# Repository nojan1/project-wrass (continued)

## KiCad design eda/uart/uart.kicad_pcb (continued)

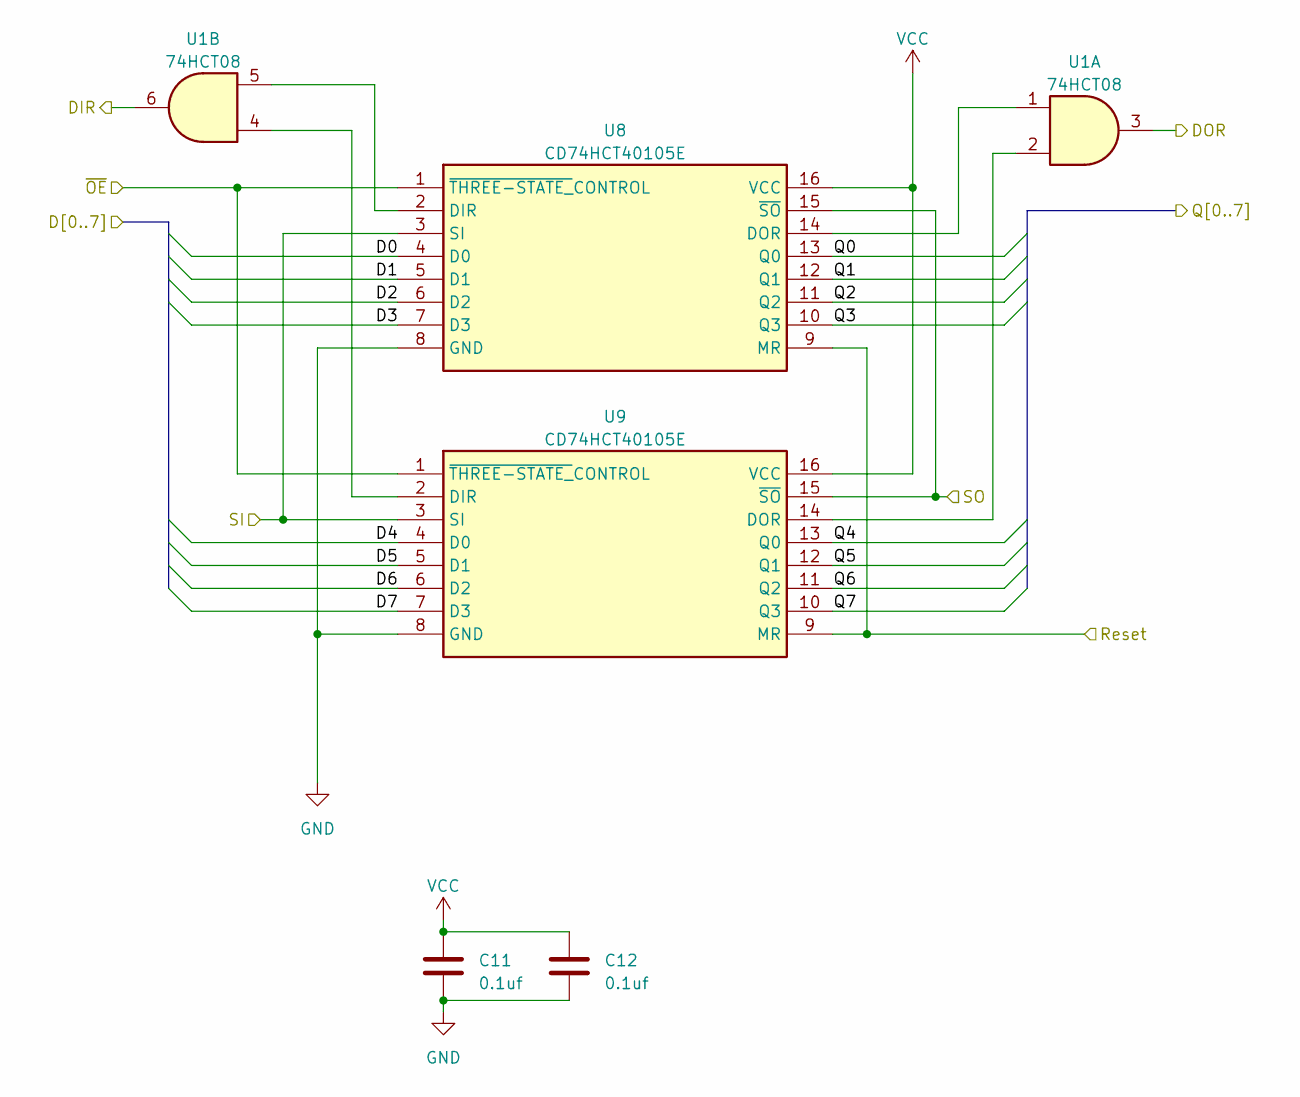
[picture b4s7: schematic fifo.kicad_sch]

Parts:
C11, C12: 0.1uf; C_Disc_D3.8mm_W2.6mm_P2.50mm
U1: 74HCT08; DIP-14_W7.62mm
U8, U9: CD74HCT40105E; DIP-16_W7.62mm; Manufacturer_Part_Number CD74HCT40105E; Mouser Part Number 595-CD74HCT40105E

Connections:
/Expansion header/D0: U8.4 (D0); also elsewhere on the board
/Expansion header/D1: U8.5 (D1); also elsewhere on the board
/Expansion header/D2: U8.6 (D2); also elsewhere on the board
/Expansion header/D3: U8.7 (D3); also elsewhere on the board
/Expansion header/D4: U9.4 (D0); also elsewhere on the board
/Expansion header/D5: U9.5 (D1); also elsewhere on the board
/Expansion header/D6: U9.6 (D2); also elsewhere on the board
/Expansion header/D7: U9.7 (D3); also elsewhere on the board
/address_decode/TransmitEnable: U8.3 (SI), U9.3 (SI); also elsewhere on the board
/recieve/DataAvailable: U1.11; also elsewhere on the board
/recieve/RecieveBufferFull: U1.8; also elsewhere on the board
/recieve/Reset: U8.9 (MR), U9.9 (MR); also elsewhere on the board
/transmit/FIFO Transmit/DOR: U1.3; also elsewhere on the board
/transmit/FIFO Transmit/Q0: U8.13 (Q0); also elsewhere on the board
/transmit/FIFO Transmit/Q1: U8.12 (Q1); also elsewhere on the board
/transmit/FIFO Transmit/Q2: U8.11 (Q2); also elsewhere on the board
/transmit/FIFO Transmit/Q3: U8.10 (Q3); also elsewhere on the board
/transmit/FIFO Transmit/Q4: U9.13 (Q0); also elsewhere on the board
/transmit/FIFO Transmit/Q5: U9.12 (Q1); also elsewhere on the board
/transmit/FIFO Transmit/Q6: U9.11 (Q2); also elsewhere on the board
/transmit/FIFO Transmit/Q7: U9.10 (Q3); also elsewhere on the board
/transmit/InputBufferFull: U1.6; also elsewhere on the board
/transmit/~LatchShiftRegisters: U8.15 (~SO), U9.15 (~SO); also elsewhere on the board
GND: C11.2, C12.2, U8.1 (~THREE-STATE_CONTROL), U8.8 (GND), U9.1 (~THREE-STATE_CONTROL), U9.8 (GND); also elsewhere on the board
unnamed: U1.5, U8.2 (DIR)
unnamed: U1.1, U8.14 (DOR)
unnamed: U1.4, U9.2 (DIR)
unnamed: U1.2, U9.14 (DOR)
unnamed 91: U1.10; also elsewhere on the board
unnamed 92: U1.12; also elsewhere on the board
unnamed 93: U1.9; also elsewhere on the board
unnamed 94: U1.13; also elsewhere on the board
VCC: C11.1, C12.1, U8.16 (VCC), U9.16 (VCC); also elsewhere on the board

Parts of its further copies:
C13, C14: 0.1uf; C_Disc_D3.8mm_W2.6mm_P2.50mm
U13, U14: CD74HCT40105E; DIP-16_W7.62mm; Manufacturer_Part_Number CD74HCT40105E; Mouser Part Number 595-CD74HCT40105E

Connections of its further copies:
/Expansion header/D0: U13.13 (Q0); also elsewhere on the board
/Expansion header/D1: U13.12 (Q1); also elsewhere on the board
/Expansion header/D2: U13.11 (Q2); also elsewhere on the board
/Expansion header/D3: U13.10 (Q3); also elsewhere on the board
/Expansion header/D4: U14.13 (Q0); also elsewhere on the board
/Expansion header/D5: U14.12 (Q1); also elsewhere on the board
/Expansion header/D6: U14.11 (Q2); also elsewhere on the board
/Expansion header/D7: U14.10 (Q3); also elsewhere on the board
/address_decode/~RecieveEnable: U13.1 (~THREE-STATE_CONTROL), U14.1 (~THREE-STATE_CONTROL); also elsewhere on the board
/recieve/FIFO Recieve/SI: U13.3 (SI), U14.3 (SI); also elsewhere on the board
/recieve/FIFO Recieve/SO: U13.15 (~SO), U14.15 (~SO); also elsewhere on the board
/recieve/ID0: U13.4 (D0); also elsewhere on the board
/recieve/ID1: U13.5 (D1); also elsewhere on the board
/recieve/ID2: U13.6 (D2); also elsewhere on the board
/recieve/ID3: U13.7 (D3); also elsewhere on the board
/recieve/ID4: U14.4 (D0); also elsewhere on the board
/recieve/ID5: U14.5 (D1); also elsewhere on the board
/recieve/ID6: U14.6 (D2); also elsewhere on the board
/recieve/ID7: U14.7 (D3); also elsewhere on the board
/recieve/Reset: U13.9 (MR), U14.9 (MR); also elsewhere on the board
GND: C13.2, C14.2, U13.8 (GND), U14.8 (GND); also elsewhere on the board
unnamed 91: U13.2 (DIR); also elsewhere on the board
unnamed 92: U13.14 (DOR); also elsewhere on the board
unnamed 93: U14.2 (DIR); also elsewhere on the board
unnamed 94: U14.14 (DOR); also elsewhere on the board
VCC: C13.1, C14.1, U13.16 (VCC), U14.16 (VCC); also elsewhere on the board

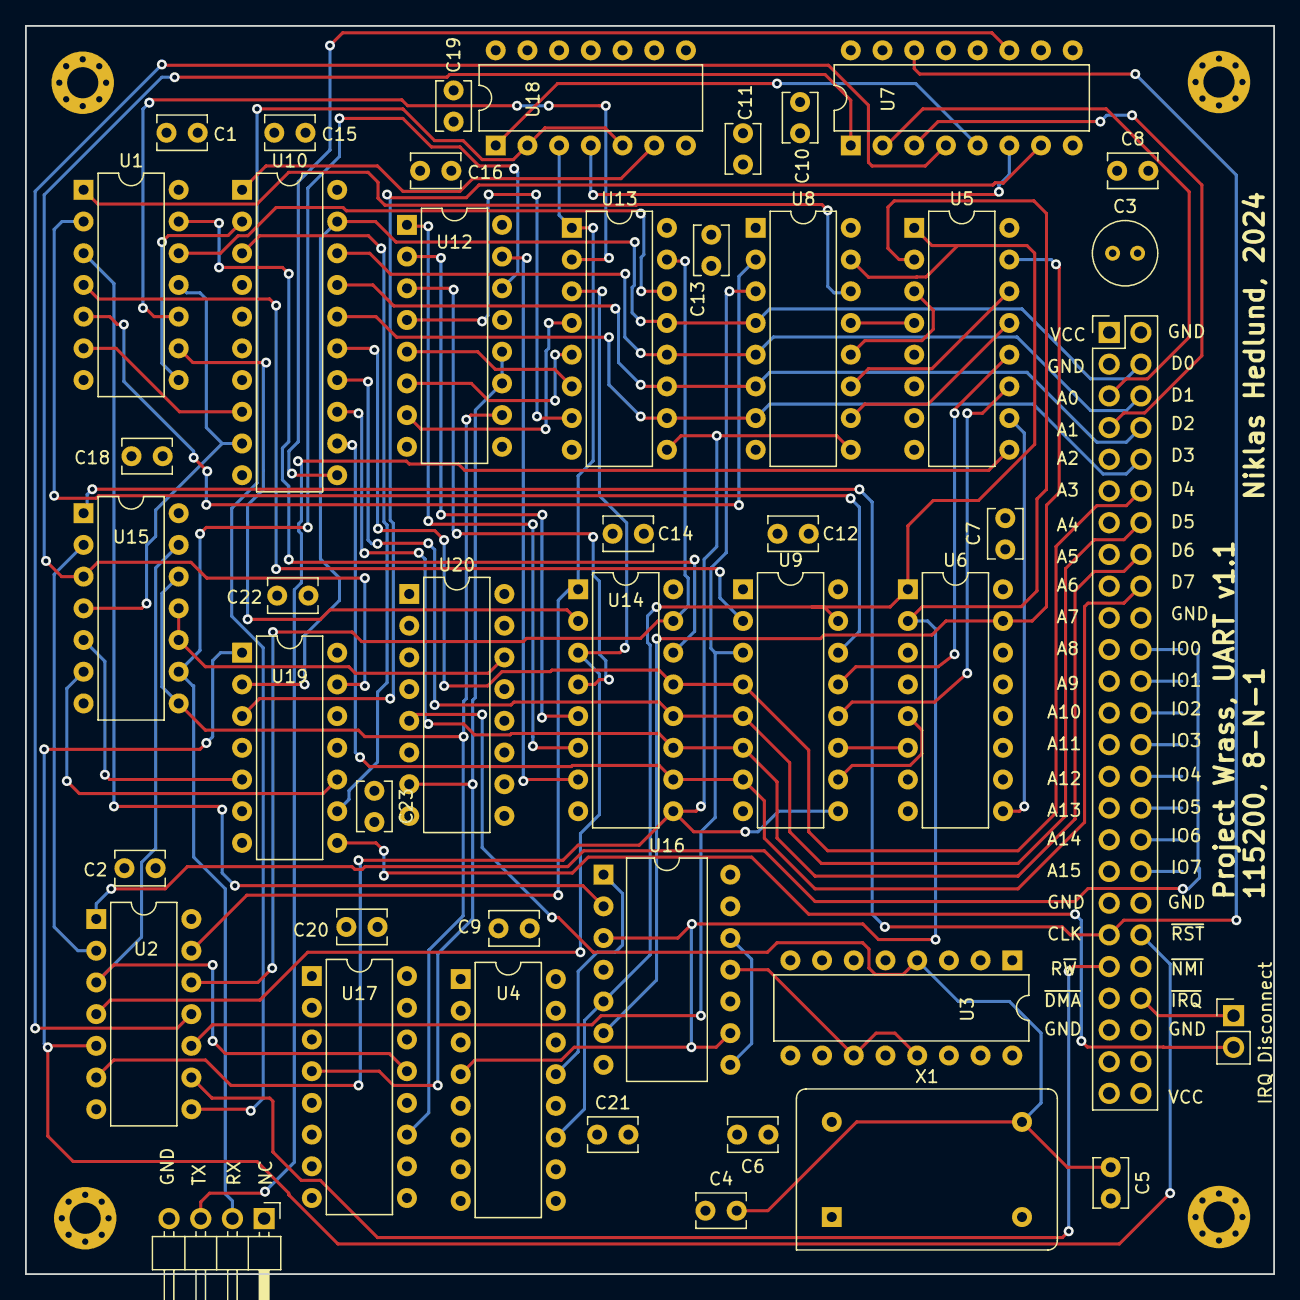
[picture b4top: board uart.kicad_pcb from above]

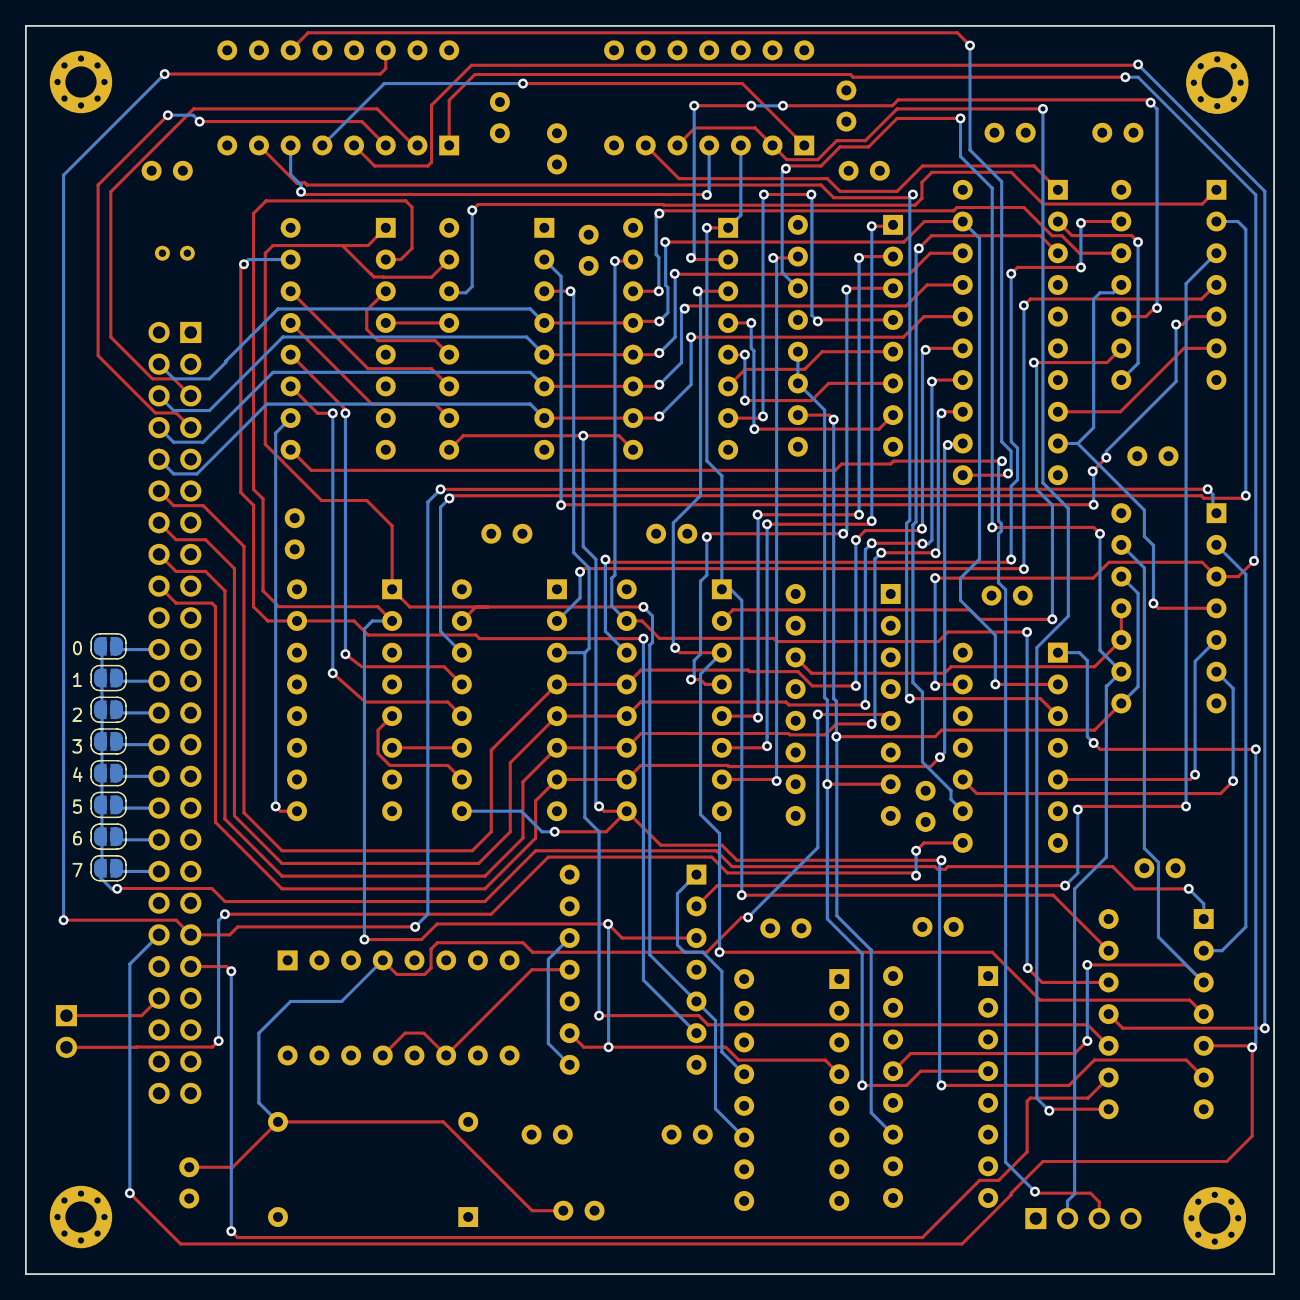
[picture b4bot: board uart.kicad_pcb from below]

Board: 4 copper layers, 100.0 x 100.0 mm, 57 parts (8 on the bottom side), 85 nets.

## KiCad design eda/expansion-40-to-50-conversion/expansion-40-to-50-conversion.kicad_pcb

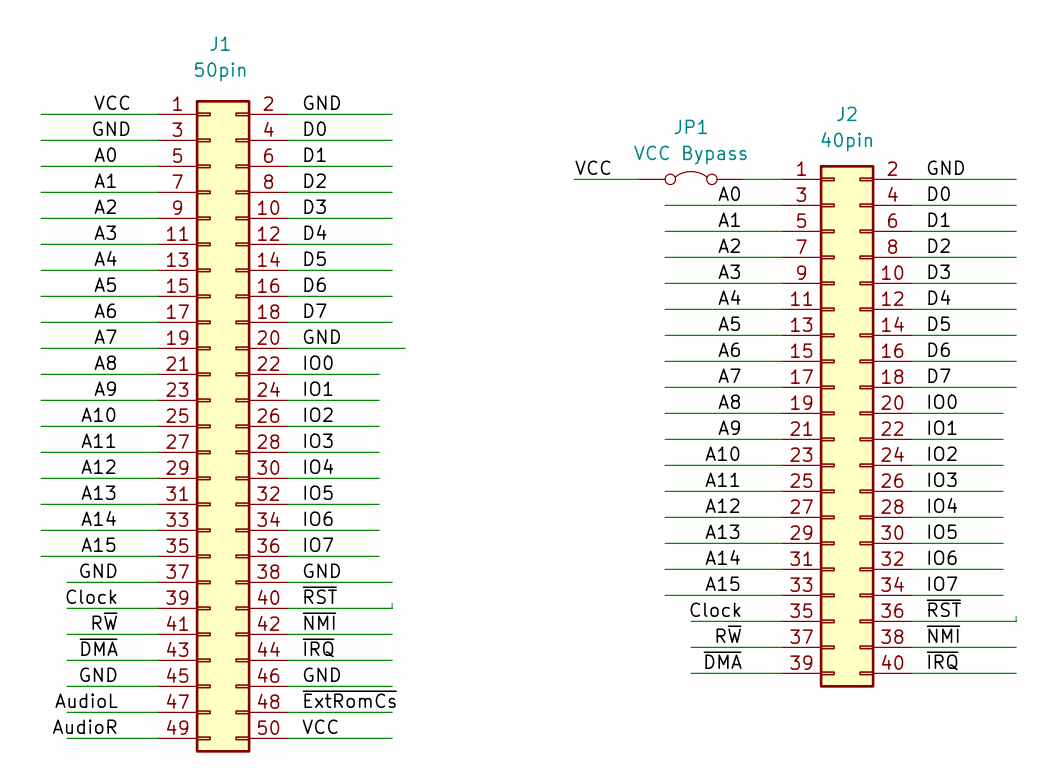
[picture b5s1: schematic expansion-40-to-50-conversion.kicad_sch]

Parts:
J1: 50pin; PinHeader_2x25_P2.54mm_Vertical
J2: 40pin; PinHeader_2x20_P2.54mm_Vertical
JP1: VCC Bypass; PinHeader_1x02_P2.54mm_Horizontal

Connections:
/A0: J1.5, J2.3
/A1: J1.7, J2.5
/A2: J1.9, J2.7
/A3: J1.11, J2.9
/A4: J1.13, J2.11
/A5: J1.15, J2.13
/A6: J1.17, J2.15
/A7: J1.19, J2.17
/A8: J1.21, J2.19
/A9: J1.23, J2.21
/A10: J1.25, J2.23
/A11: J1.27, J2.25
/A12: J1.29, J2.27
/A13: J1.31, J2.29
/A14: J1.33, J2.31
/A15: J1.35, J2.33
/AudioL: J1.47
/AudioR: J1.49
/Clock: J1.39, J2.35
/D0: J1.4, J2.4
/D1: J1.6, J2.6
/D2: J1.8, J2.8
/D3: J1.10, J2.10
/D4: J1.12, J2.12
/D5: J1.14, J2.14
/D6: J1.16, J2.16
/D7: J1.18, J2.18
/GND: J1.2, J1.3, J1.20, J1.37, J1.38, J1.45, J1.46, J2.2
/IO0: J1.22, J2.20
/IO1: J1.24, J2.22
/IO2: J1.26, J2.24
/IO3: J1.28, J2.26
/IO4: J1.30, J2.28
/IO5: J1.32, J2.30
/IO6: J1.34, J2.32
/IO7: J1.36, J2.34
/R~W: J1.41, J2.37
/VCC: J1.1, J1.50, JP1.1 (A)
/~DMA: J1.43, J2.39
/~ExtRomCs: J1.48
/~IRQ: J1.44, J2.40
/~NMI: J1.42, J2.38
/~RST: J1.40, J2.36
unnamed: J2.1, JP1.2 (B)

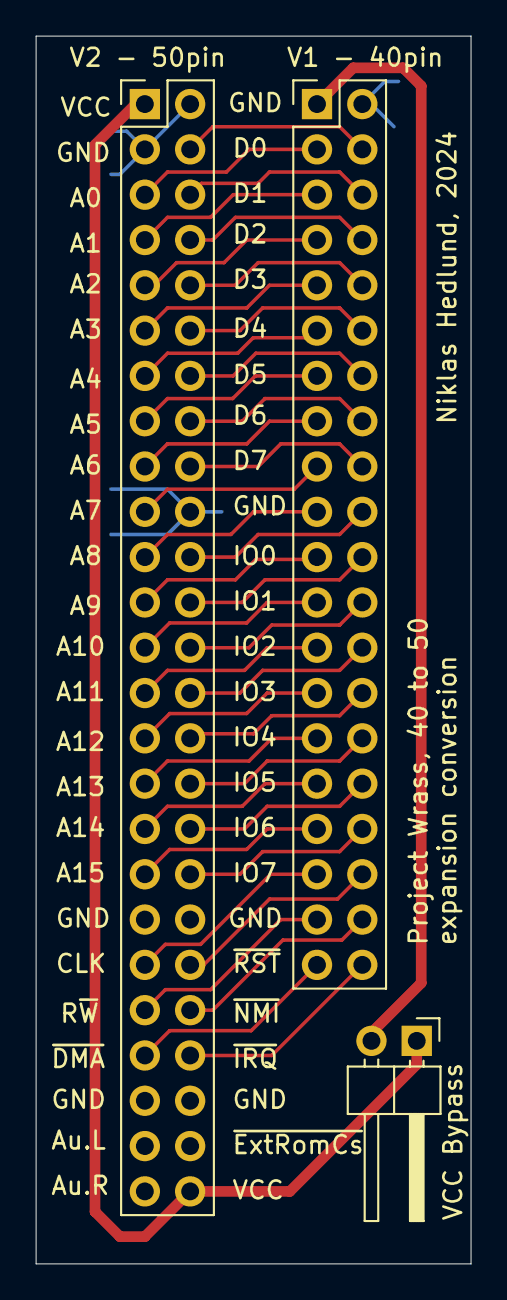
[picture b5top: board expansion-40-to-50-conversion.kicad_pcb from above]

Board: 2 copper layers, 24.4 x 68.8 mm, 3 parts (0 on the bottom side), 41 nets.

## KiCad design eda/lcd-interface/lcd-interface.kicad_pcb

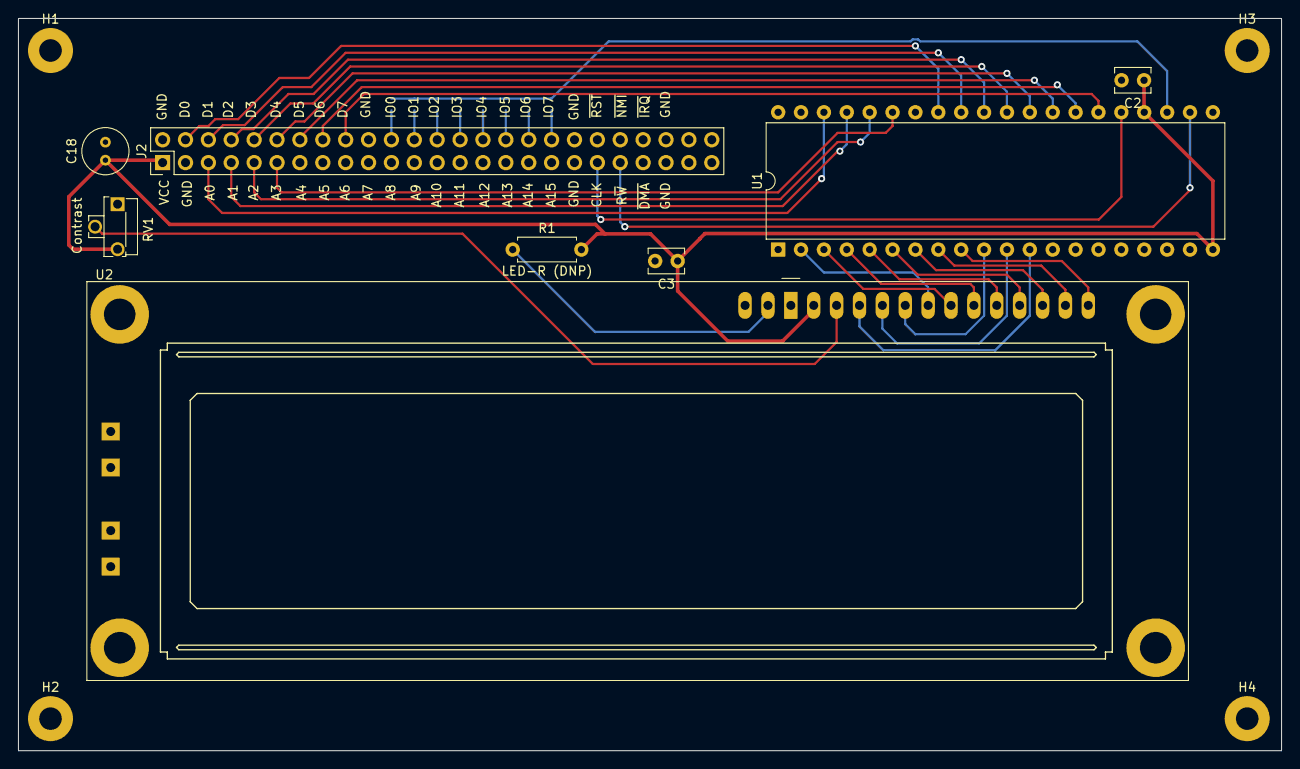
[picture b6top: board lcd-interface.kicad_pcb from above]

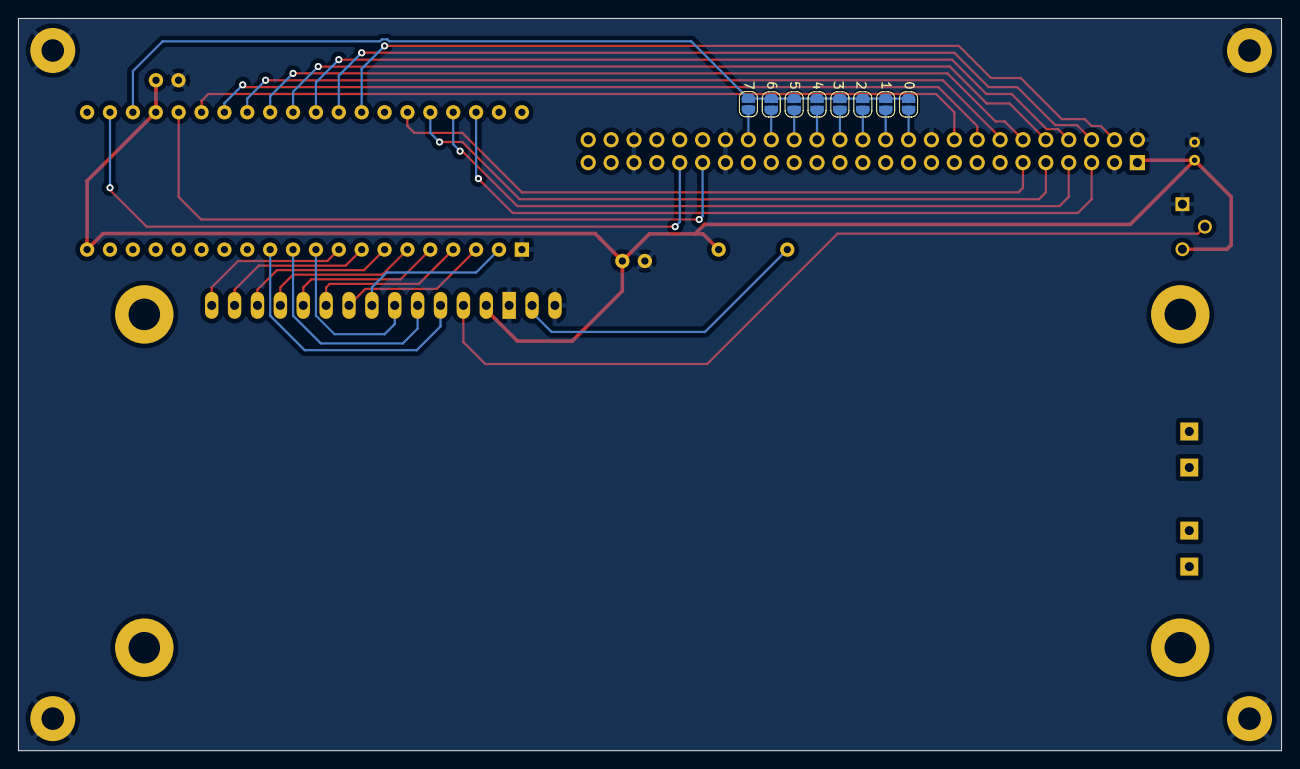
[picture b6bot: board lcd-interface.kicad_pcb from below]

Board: 2 copper layers, 140.2 x 81.3 mm, 20 parts (8 on the bottom side), 39 nets.

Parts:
C2, C3: 100nf; C_Disc_D3.8mm_W2.6mm_P2.50mm
C18: 100nf; C_Radial_D5.0mm_H7.0mm_P2.00mm
H1, H2, H3, H4: MountingHole_Pad; MountingHole_2.5mm_Pad
J2: Conn_02x25_Odd_Even; PinHeader_2x25_P2.54mm_Vertical
JP1, JP2, JP3, JP4, JP5, JP6, JP7, JP8: SolderJumper_2_Open; SolderJumper-2_P1.3mm_Open_RoundedPad1.0x1.5mm
R1: LED-R (DNP); R_Axial_DIN0207_L6.3mm_D2.5mm_P7.62mm_Horizontal
RV1: Contrast; Potentiometer_Runtron_RM-063_Horizontal
U1: W65C22SxP; DIP-40_W15.24mm
U2: LCD-016N002L

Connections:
/Clock: J2.39, U1.25 (ϕ2)
/Expansion header/A0: J2.5, U1.38 (RS0)
/Expansion header/A1: J2.7, U1.37 (RS1)
/Expansion header/A2: J2.9, U1.36 (RS2)
/Expansion header/A3: J2.11, U1.35 (RS3)
/Expansion header/D0: J2.4, U1.33 (D0)
/Expansion header/D1: J2.6, U1.32 (D1)
/Expansion header/D2: J2.8, U1.31 (D2)
/Expansion header/D3: J2.10, U1.30 (D3)
/Expansion header/D4: J2.12, U1.29 (D4)
/Expansion header/D5: J2.14, U1.28 (D5)
/Expansion header/D6: J2.16, U1.27 (D6)
/Expansion header/D7: J2.18, U1.26 (D7)
/R~W: J2.41, U1.22 (R/~W)
/~CS: JP1.2 (B), JP2.2 (B), JP3.2 (B), JP4.2 (B), JP5.2 (B), JP6.2 (B), JP7.2 (B), JP8.2 (B), U1.23 (~CS2)
/~RST: J2.40, U1.34 (~RES)
GND: C2.2, C3.2, C18.2, H1.1, H2.1, H3.1, H4.1, J2.2, J2.3, J2.20, J2.37, J2.38, J2.45, J2.46, RV1.1, U1.1 (VSS), U2.1 (VSS), U2.16 (K)
unnamed: J2.22, JP1.1 (A)
unnamed: J2.24, JP2.1 (A)
unnamed: J2.26, JP3.1 (A)
unnamed: J2.28, JP4.1 (A)
unnamed: J2.30, JP5.1 (A)
unnamed: J2.32, JP6.1 (A)
unnamed: J2.34, JP7.1 (A)
unnamed: J2.36, JP8.1 (A)
unnamed: U1.2 (PA0), U2.7 (DB0)
unnamed: U1.3 (PA1), U2.8 (DB1)
unnamed: U1.4 (PA2), U2.9 (DB2)
unnamed: U1.5 (PA3), U2.10 (DB3)
unnamed: U1.6 (PA4), U2.11 (DB4)
unnamed: U1.7 (PA5), U2.12 (DB5)
unnamed: U1.8 (PA6), U2.13 (DB6)
unnamed: U1.9 (PA7), U2.14 (DB7)
unnamed: U1.10 (PB0), U2.6 (E)
unnamed: U1.11 (PB1), U2.5 (R/~W)
unnamed: U1.12 (PB2), U2.4 (RS)
unnamed: R1.1, U2.15 (A/VEE)
unnamed: RV1.2, U2.3 (VO)
VCC: C2.1, C3.1, C18.1, J2.1, R1.2, RV1.3, U1.20 (VCC), U1.24 (CS1), U2.2 (VDD)

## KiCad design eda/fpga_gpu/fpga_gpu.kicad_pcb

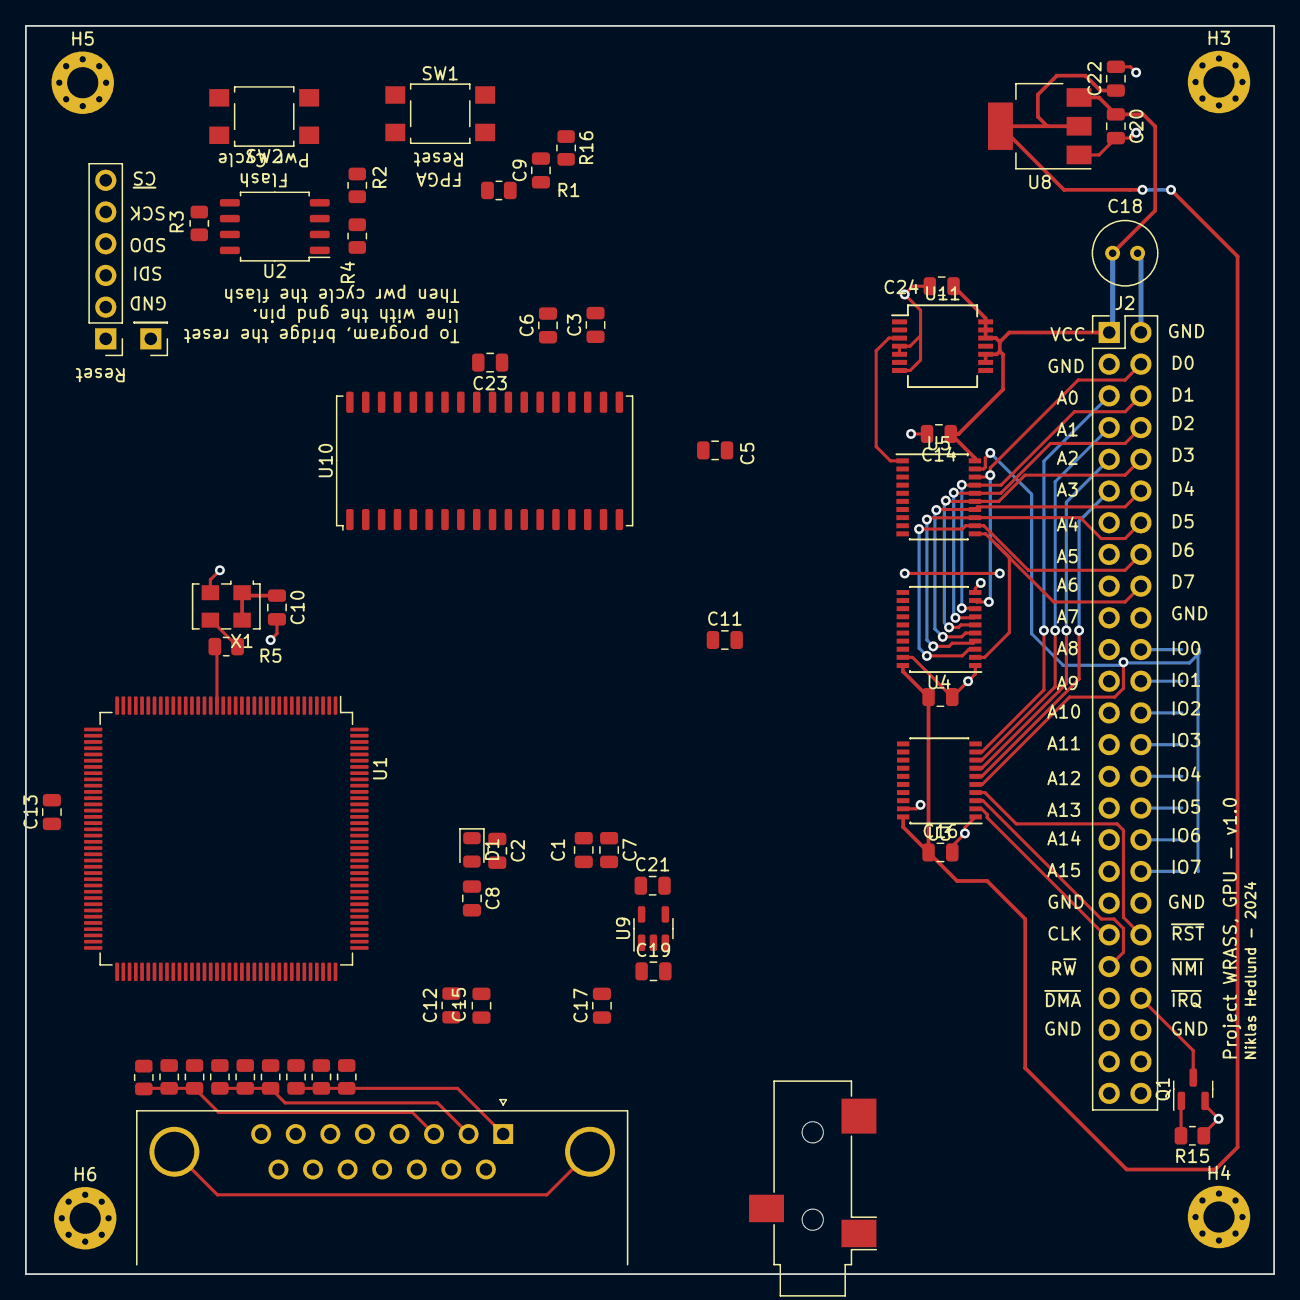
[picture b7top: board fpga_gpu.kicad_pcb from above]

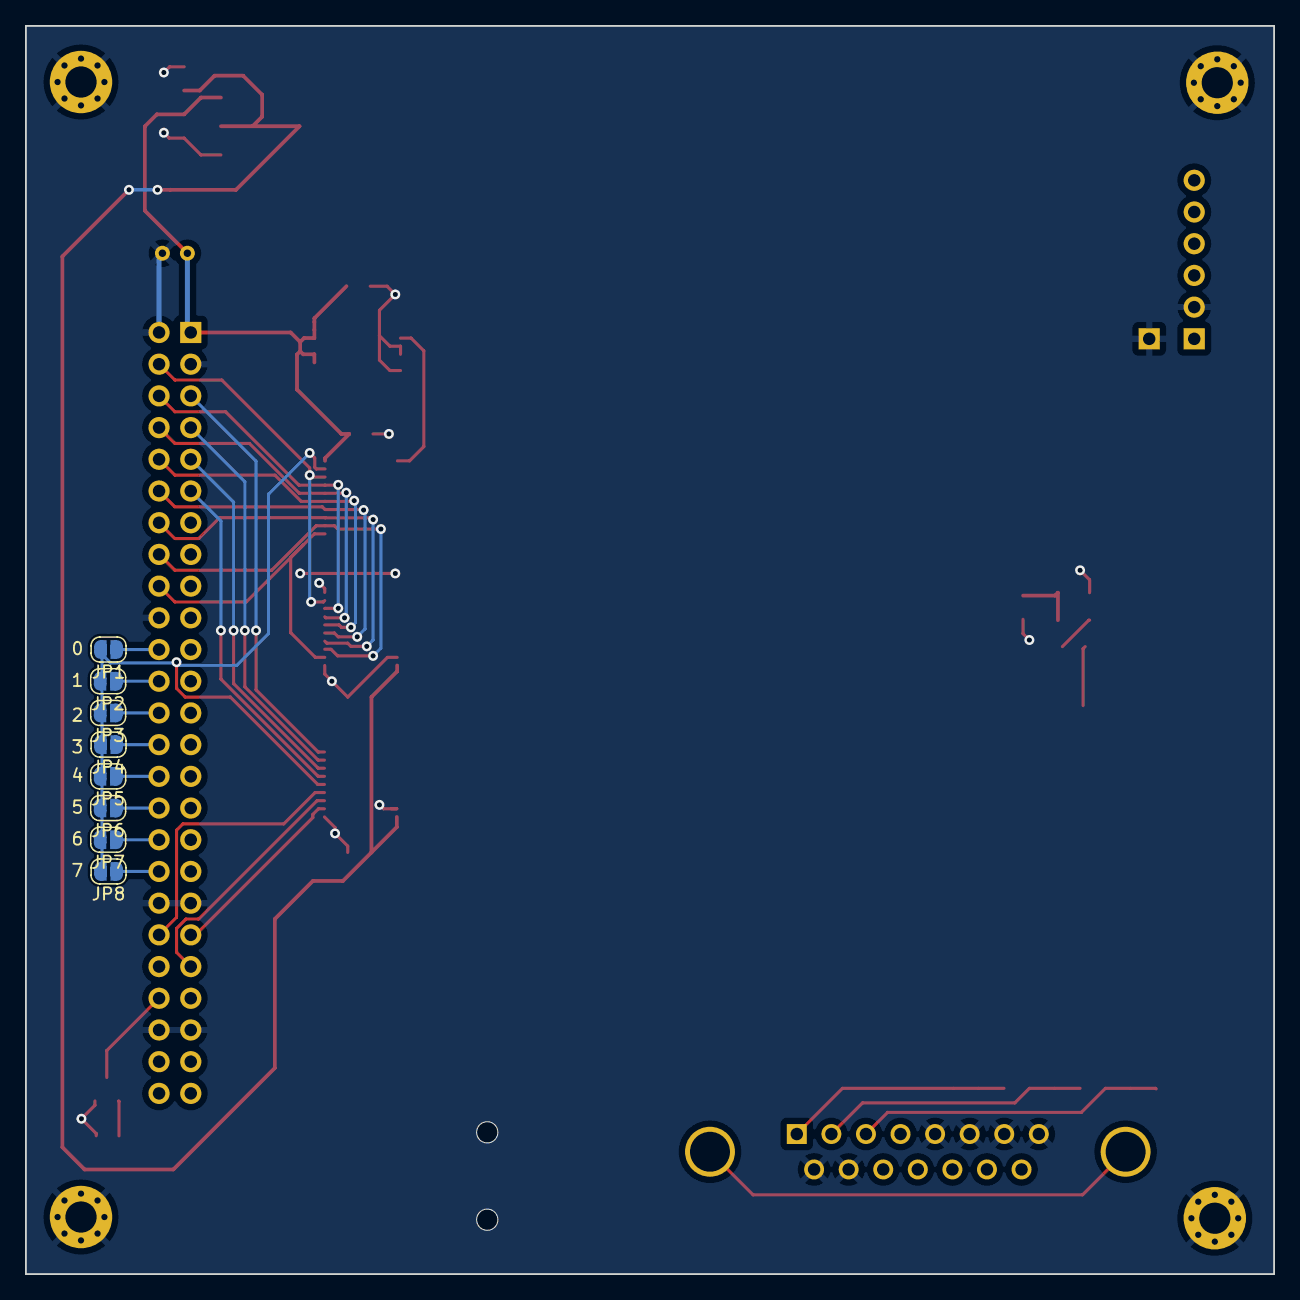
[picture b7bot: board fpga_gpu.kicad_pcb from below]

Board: 2 copper layers, 100.0 x 100.0 mm, 71 parts (8 on the bottom side), 111 nets.

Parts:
C1, C2, C3, C4, C5, C6, C7, C8, C9, C10, C11, C12, C13, C14, C15, C16, C17, C23, C24: 100n; C_0805_2012Metric
C18: 100nf; C_Radial_D5.0mm_H7.0mm_P2.00mm
C19, C20, C21, C22: 22u; C_0805_2012Metric
D1: 1N5817; D_0805_2012Metric
H3, H4, H5, H6: MountingHole_Pad; MountingHole_2.5mm_Pad_Via
J1: VGA; DSUB-15_Female_Horizontal_P2.77x2.84mm_EdgePinOffset7.70mm_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
J2: Conn_02x25_Odd_Even; PinHeader_2x25_P2.54mm_Vertical
J3: programming; PinHeader_1x06_P2.54mm_Vertical
J4: reset ground; PinHeader_1x01_P2.54mm_Vertical
J5: AudioPlug3; Jack_3.5mm_CUI_SJ-3523-SMT_Horizontal
JP1, JP2, JP3, JP4, JP5, JP6, JP7, JP8: SolderJumper_2_Open; SolderJumper-2_P1.3mm_Open_RoundedPad1.0x1.5mm
Q1: 2N7002; SOT-23
R1, R5: 22R; R_0805_2012Metric
R2, R3, R4, R15, R16: 10k; R_0805_2012Metric
R6, R9, R12: 470; R_0805_2012Metric
R7, R10, R13: 1k; R_0805_2012Metric
R8, R11, R14: 1k8; R_0805_2012Metric
SW1: SW_Reset; SW_SPST_TL3305A
SW2: SW_FlashPwrCycle; SW_SPST_TL3305A
U1: ICE40HX4K-TQ144; TQFP-144_20x20mm_P0.5mm
U2: SST25VF080B-50-4x-S2Ax; SOIC-8_5.275x5.275mm_P1.27mm
U3, U4: 74HC541; SSOP-20_4.4x6.5mm_P0.65mm
U5: 74HCT541; SSOP-20_4.4x6.5mm_P0.65mm
U8: AMS1117-3.3; SOT-223-3_TabPin2
U9: AP2112K-1.2; SOT-23-5
U10: IS61C5128AL-10KLI; SOJ-36_10.16x23.49mm_P1.27mm
U11: 74HCT00; SSOP-14_5.3x6.2mm_P0.65mm
X1: TXC-7C; Oscillator_SMD_TXC_7C-4Pin_5.0x3.2mm

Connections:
+1V2: C5.1, C6.1, C7.1, C21.1, U1.27 (VCC), U1.40 (VCC), U1.54 (VCCPLL0), U1.92 (VCC), U1.111 (VCC), U1.126 (VCCPLL1), U9.5 (VOUT)
+3.3V: C1.1, C2.1, C3.1, C4.1, C8.1, C9.1, C10.1, C16.1, C17.1, C22.1, D1.2 (A), R16.2, SW2.2 (B), U1.6 (VCCIO_3), U1.30 (VCCIO_3), U1.46 (VCCIO_2), U1.57 (VCCIO_2), U1.72 (VCC_SPI), U1.89 (VCCIO_1), U1.100 (VCCIO_1), U1.123 (VCCIO_0), U1.131 (VCCIO_0), U3.20 (VCC), U4.20 (VCC), U8.2 (VO), X1.1 (EN), X1.4 (Vdd)
/DIn0: U1.88 (IOR_137), U4.11 (Y7)
/DIn1: U1.90 (IOR_138), U4.12 (Y6)
/DIn2: U1.91 (IOR_139), U4.13 (Y5)
/DIn3: U1.93 (IOR_140_GBIN3), U4.14 (Y4)
/DIn4: U1.94 (IOR_141_GBIN2), U4.15 (Y3)
/DIn5: U1.95 (IOR_144), U4.16 (Y2)
/DIn6: U1.96 (IOR_146), U4.17 (Y1)
/DIn7: U1.97 (IOR_147), U4.18 (Y0)
/DOut0: U1.98 (IOR_148), U5.2 (A0)
/DOut1: U1.99 (IOR_152), U5.3 (A1)
/DOut2: U1.101 (IOR_160), U5.4 (A2)
/DOut3: U1.102 (IOR_161), U5.5 (A3)
/DOut4: U1.104 (IOR_164), U5.6 (A4)
/DOut5: U1.105 (IOR_165), U5.7 (A5)
/DOut6: U1.106 (IOR_166), U5.8 (A6)
/DOut7: U1.107 (IOR_167), U5.9 (A7)
/FpgaIRQ: Q1.1 (G), R15.2, U1.74 (IOR_110)
/HSYNC: J1.14, U1.75 (IOR_111)
/Interfacing/ADev0: U1.118 (IOT_177), U3.11 (Y7)
/Interfacing/ADev1: U1.117 (IOT_174), U3.12 (Y6)
/Interfacing/ADev2: U1.116 (IOT_173), U3.13 (Y5)
/Interfacing/ADev3: U1.115 (IOT_172), U3.14 (Y4)
/Interfacing/Clock: U1.129 (IOT_198_GBIN0), U3.18 (Y0)
/Interfacing/Clock-VCC: J2.39, U3.2 (A0), U11.2
/Interfacing/Expansion/A0: J2.5, U3.9 (A7)
/Interfacing/Expansion/A1: J2.7, U3.8 (A6)
/Interfacing/Expansion/A2: J2.9, U3.7 (A5)
/Interfacing/Expansion/A3: J2.11, U3.6 (A4)
/Interfacing/Expansion/D0: J2.4, U4.9 (A7), U5.18 (Y0)
/Interfacing/Expansion/D1: J2.6, U4.8 (A6), U5.17 (Y1)
/Interfacing/Expansion/D2: J2.8, U4.7 (A5), U5.16 (Y2)
/Interfacing/Expansion/D3: J2.10, U4.6 (A4), U5.15 (Y3)
/Interfacing/Expansion/D4: J2.12, U4.5 (A3), U5.14 (Y4)
/Interfacing/Expansion/D5: J2.14, U4.4 (A2), U5.13 (Y5)
/Interfacing/Expansion/D6: J2.16, U4.3 (A1), U5.12 (Y6)
/Interfacing/Expansion/D7: J2.18, U4.2 (A0), U5.11 (Y7)
/Interfacing/Expansion/~RST: J2.40, U3.4 (A2)
/Interfacing/R~W: U1.112 (IOT_169), U3.17 (Y1)
/Interfacing/R~W-VCC: J2.41, U3.3 (A1), U11.1
/Interfacing/~CS: U1.114 (IOT_171), U3.15 (Y3)
/Interfacing/~CS-VCC: JP1.2 (B), JP2.2 (B), JP3.2 (B), JP4.2 (B), JP5.2 (B), JP6.2 (B), JP7.2 (B), JP8.2 (B), U3.5 (A3), U5.19 (G2)
/Interfacing/~IRQ: J2.44, Q1.3 (D)
/Interfacing/~RST: U1.113 (IOT_170), U3.16 (Y2)
/RamA0: U1.18 (IOL_12B), U10.1 (A0)
/RamA1: U1.17 (IOL_12A), U10.2 (A1)
/RamA2: U1.16 (IOL_10B), U10.3 (A2)
/RamA3: U1.15 (IOL_10A), U10.4 (A3)
/RamA4: U1.12 (IOL_8B), U10.5 (A4)
/RamA5: U1.11 (IOL_8A), U10.14 (A5)
/RamA6: U1.10 (IOL_5B), U10.15 (A6)
/RamA7: U1.9 (IOL_5A), U10.16 (A7)
/RamA8: U1.8 (IOL_4B), U10.17 (A8)
/RamA9: U1.7 (IOL_4A), U10.18 (A9)
/RamA10: U1.19 (IOL_13A), U10.20 (A10)
/RamA11: U1.21 (IOL_14A_GBIN6), U10.21 (A11)
/RamA12: U1.22 (IOL_14B), U10.22 (A12)
/RamA13: U1.23 (IOL_17A), U10.23 (A13)
/RamA14: U1.24 (IOL_17B), U10.24 (A14)
/RamA15: U1.25 (IOL_18A), U10.32 (A15)
/RamA16: U1.29 (IOL_23B), U10.33 (A16)
/RamA17: U1.31 (IOL_24A), U10.34 (A17)
/RamA18: U1.32 (IOL_24B), U10.35 (A18)
/RamIo0: U1.61 (IOB_96), U10.7 (I/O0)
/RamIo1: U1.56 (IOB_94), U10.8 (I/O1)
/RamIo2: U1.49 (IOB_81_GBIN5), U10.11 (I/O2)
/RamIo3: U1.48 (IOB_80), U10.12 (I/O3)
/RamIo4: U1.52 (IOB_82_GBIN4), U10.25 (I/O4)
/RamIo5: U1.55 (IOB_91), U10.26 (I/O5)
/RamIo6: U1.60 (IOB_95), U10.29 (I/O6)
/RamIo7: U1.62 (IOB_102), U10.30 (I/O7)
/SYSCLOCK: R5.2, U1.20 (IOL_13B_GBIN7)
/VGA Connector/Blue0: R12.2, U1.78 (IOR_114)
/VGA Connector/Blue1: R13.2, U1.79 (IOR_115)
/VGA Connector/Blue2: R14.2, U1.80 (IOR_116)
/VGA Connector/Green0: R9.2, U1.81 (IOR_117)
/VGA Connector/Green1: R10.2, U1.82 (IOR_118)
/VGA Connector/Green2: R11.2, U1.83 (IOR_119)
/VGA Connector/Red0: R6.2, U1.84 (IOR_120)
/VGA Connector/Red1: R7.2, U1.85 (IOR_128)
/VGA Connector/Red2: R8.2, U1.87 (IOR_136)
/VSYNC: J1.13, U1.76 (IOR_112)
/~RamCE: U1.63 (IOB_103_CBSEL0), U10.6 (~CE)
/~RamOE: U1.64 (IOB_104_CBSEL1), U10.31 (~OE)
/~RamWE: U1.28 (IOL_23A), U10.13 (~WE)
GND: C1.2, C2.2, C3.2, C4.2, C5.2, C6.2, C7.2, C8.2, C9.2, C10.2, C11.2, C12.2, C13.2, C14.2, C15.2, C16.2, C17.2, C18.2, C19.2, C20.2, C21.2, C22.2, C23.2, C24.2, H3.1, H4.1, H5.1, H6.1, J1.5, J1.6, J1.7, J1.8, J1.9, J1.10, J2.2, J2.3, J2.20, J2.37, J2.38, J2.45, J2.46, J3.2, J4.1, Q1.2 (S), R4.1, R15.1, SW1.1, U1.5 (GND), U1.13 (GND), U1.14 (GND), U1.53 (GNDPLL0), U1.59 (GND), U1.69 (GND), U1.86 (GND), U1.103 (GND), U1.127 (GNDPLL1), U1.132 (GND), U1.140 (GND), U2.4 (VSS), U3.1 (G1), U3.10 (GND), U3.19 (G2), U4.1 (G1), U4.10 (GND), U4.19 (G2), U5.10 (GND), U8.1 (GND), U9.2 (GND), U10.10 (GND), U10.28 (GND), U11.4, U11.5, U11.7 (GND), X1.2 (GND)
unnamed: D1.1 (K), U1.108 (VPP_2V5)
unnamed: J1.1, R6.1, R7.1, R8.1
unnamed: J1.2, R9.1, R10.1, R11.1
unnamed: J1.3, R12.1, R13.1, R14.1
unnamed: J2.22, JP1.1 (A)
unnamed: J2.24, JP2.1 (A)
unnamed: J2.26, JP3.1 (A)
unnamed: J2.28, JP4.1 (A)
unnamed: J2.30, JP5.1 (A)
unnamed: J2.32, JP6.1 (A)
unnamed: J2.34, JP7.1 (A)
unnamed: J2.36, JP8.1 (A)
unnamed: J3.6, R1.2, R4.2, U2.1 (~CE)
unnamed: R2.2, R3.2, SW2.1 (A), U2.8 (VDD)
unnamed: R3.1, U2.7 (~HOLD)
unnamed: R2.1, U2.3 (~WP)
unnamed: U5.1 (G1), U11.3
unnamed: R5.1, X1.3 (OUT)
VCC: C11.1, C12.1, C13.1, C14.1, C15.1, C18.1, C19.1, C20.1, C23.1, C24.1, J2.1, U5.20 (VCC), U8.3 (VI), U9.1 (VIN), U9.3 (EN), U10.9 (VDD), U10.27 (VDD), U11.9, U11.10, U11.12, U11.13, U11.14 (VCC)
ice40-CRESET: J3.1, R16.1, SW1.2, U1.66 (~CRESET)
ice40-SCK: J3.5, U1.70 (IOB_107_SCK), U2.6 (SCK)
ice40-SDI: J3.3, U1.68 (IOB_106_SDI), U2.2 (SO)
ice40-SDO: J3.4, U1.67 (IOB_105_SDO), U2.5 (SI)
~ice40-CS: R1.1, U1.71 (IOB_108_SS)

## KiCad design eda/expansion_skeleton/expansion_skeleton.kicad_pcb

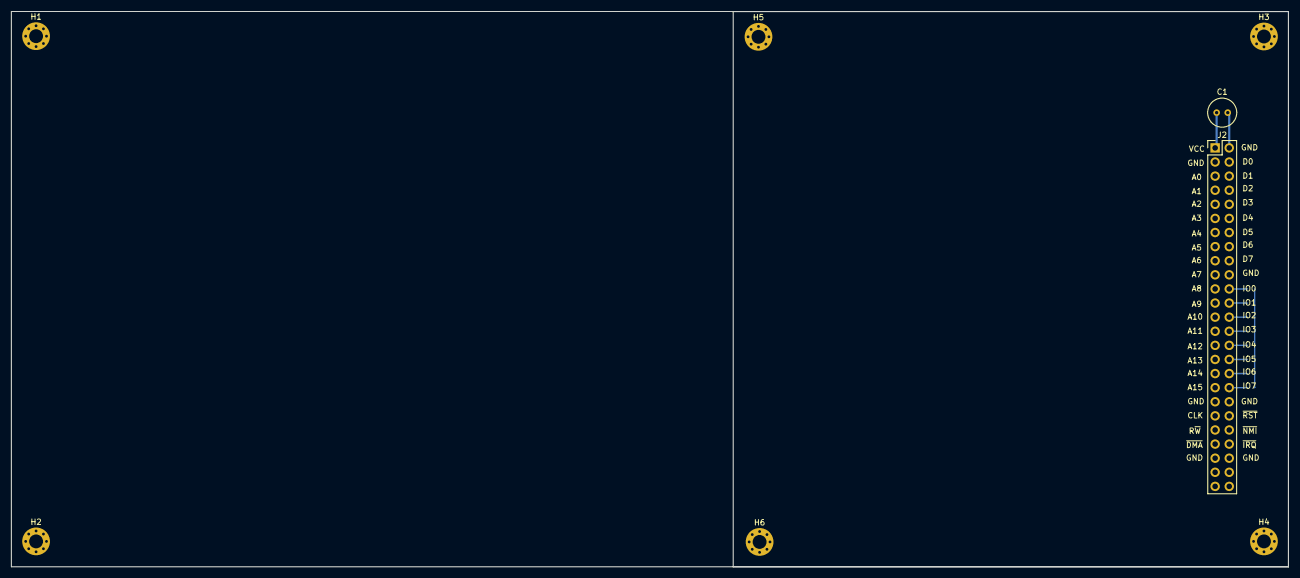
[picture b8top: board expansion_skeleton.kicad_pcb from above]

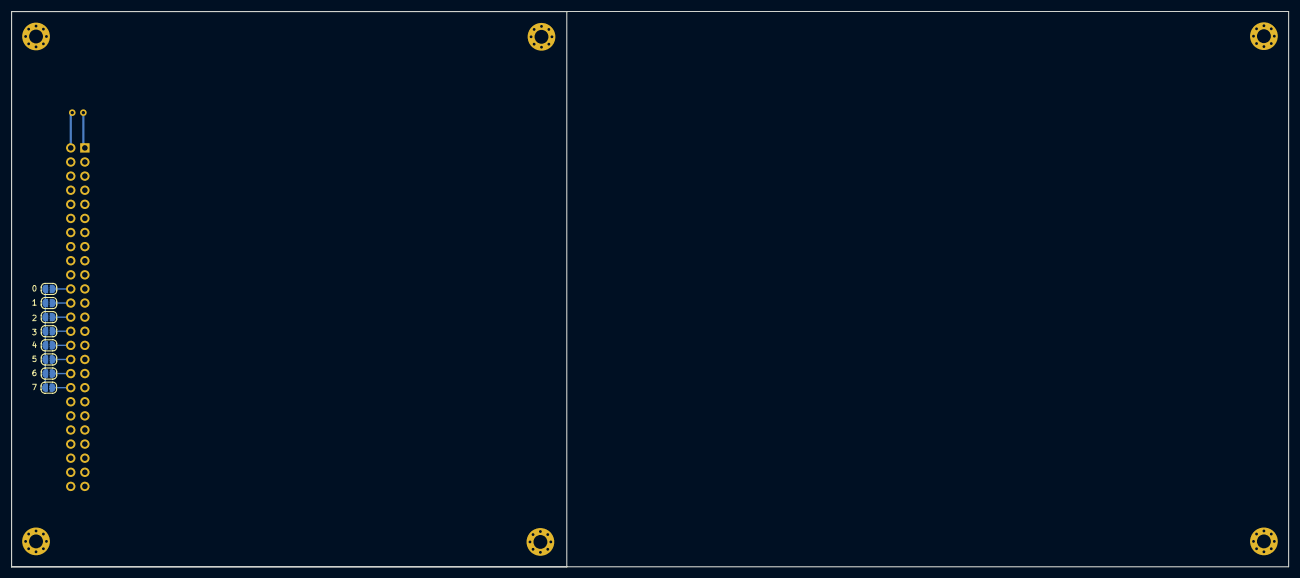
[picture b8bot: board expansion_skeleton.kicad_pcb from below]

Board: 2 copper layers, 230.0 x 100.0 mm, 16 parts (8 on the bottom side), 12 nets.

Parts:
C1: 100nf; C_Radial_D5.0mm_H7.0mm_P2.00mm
H1, H2, H3, H4, H5, H6: MountingHole_Pad; MountingHole_2.5mm_Pad_Via
J2: Conn_02x25_Odd_Even; PinHeader_2x25_P2.54mm_Vertical
JP9, JP10, JP11, JP12, JP13, JP14, JP15, JP16: SolderJumper_2_Open; SolderJumper-2_P1.3mm_Open_RoundedPad1.0x1.5mm

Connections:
/Expansion/GND: C1.2, J2.2, J2.3, J2.20, J2.37, J2.38, J2.45, J2.46
/Expansion/VCC: C1.1, J2.1
/Expansion/~CS: JP9.2 (B), JP10.2 (B), JP11.2 (B), JP12.2 (B), JP13.2 (B), JP14.2 (B), JP15.2 (B), JP16.2 (B)
GND: H1.1, H2.1, H3.1, H4.1, H5.1, H6.1
unnamed: J2.22, JP9.1 (A)
unnamed: J2.24, JP10.1 (A)
unnamed: J2.26, JP11.1 (A)
unnamed: J2.28, JP12.1 (A)
unnamed: J2.30, JP13.1 (A)
unnamed: J2.32, JP14.1 (A)
unnamed: J2.34, JP15.1 (A)
unnamed: J2.36, JP16.1 (A)
